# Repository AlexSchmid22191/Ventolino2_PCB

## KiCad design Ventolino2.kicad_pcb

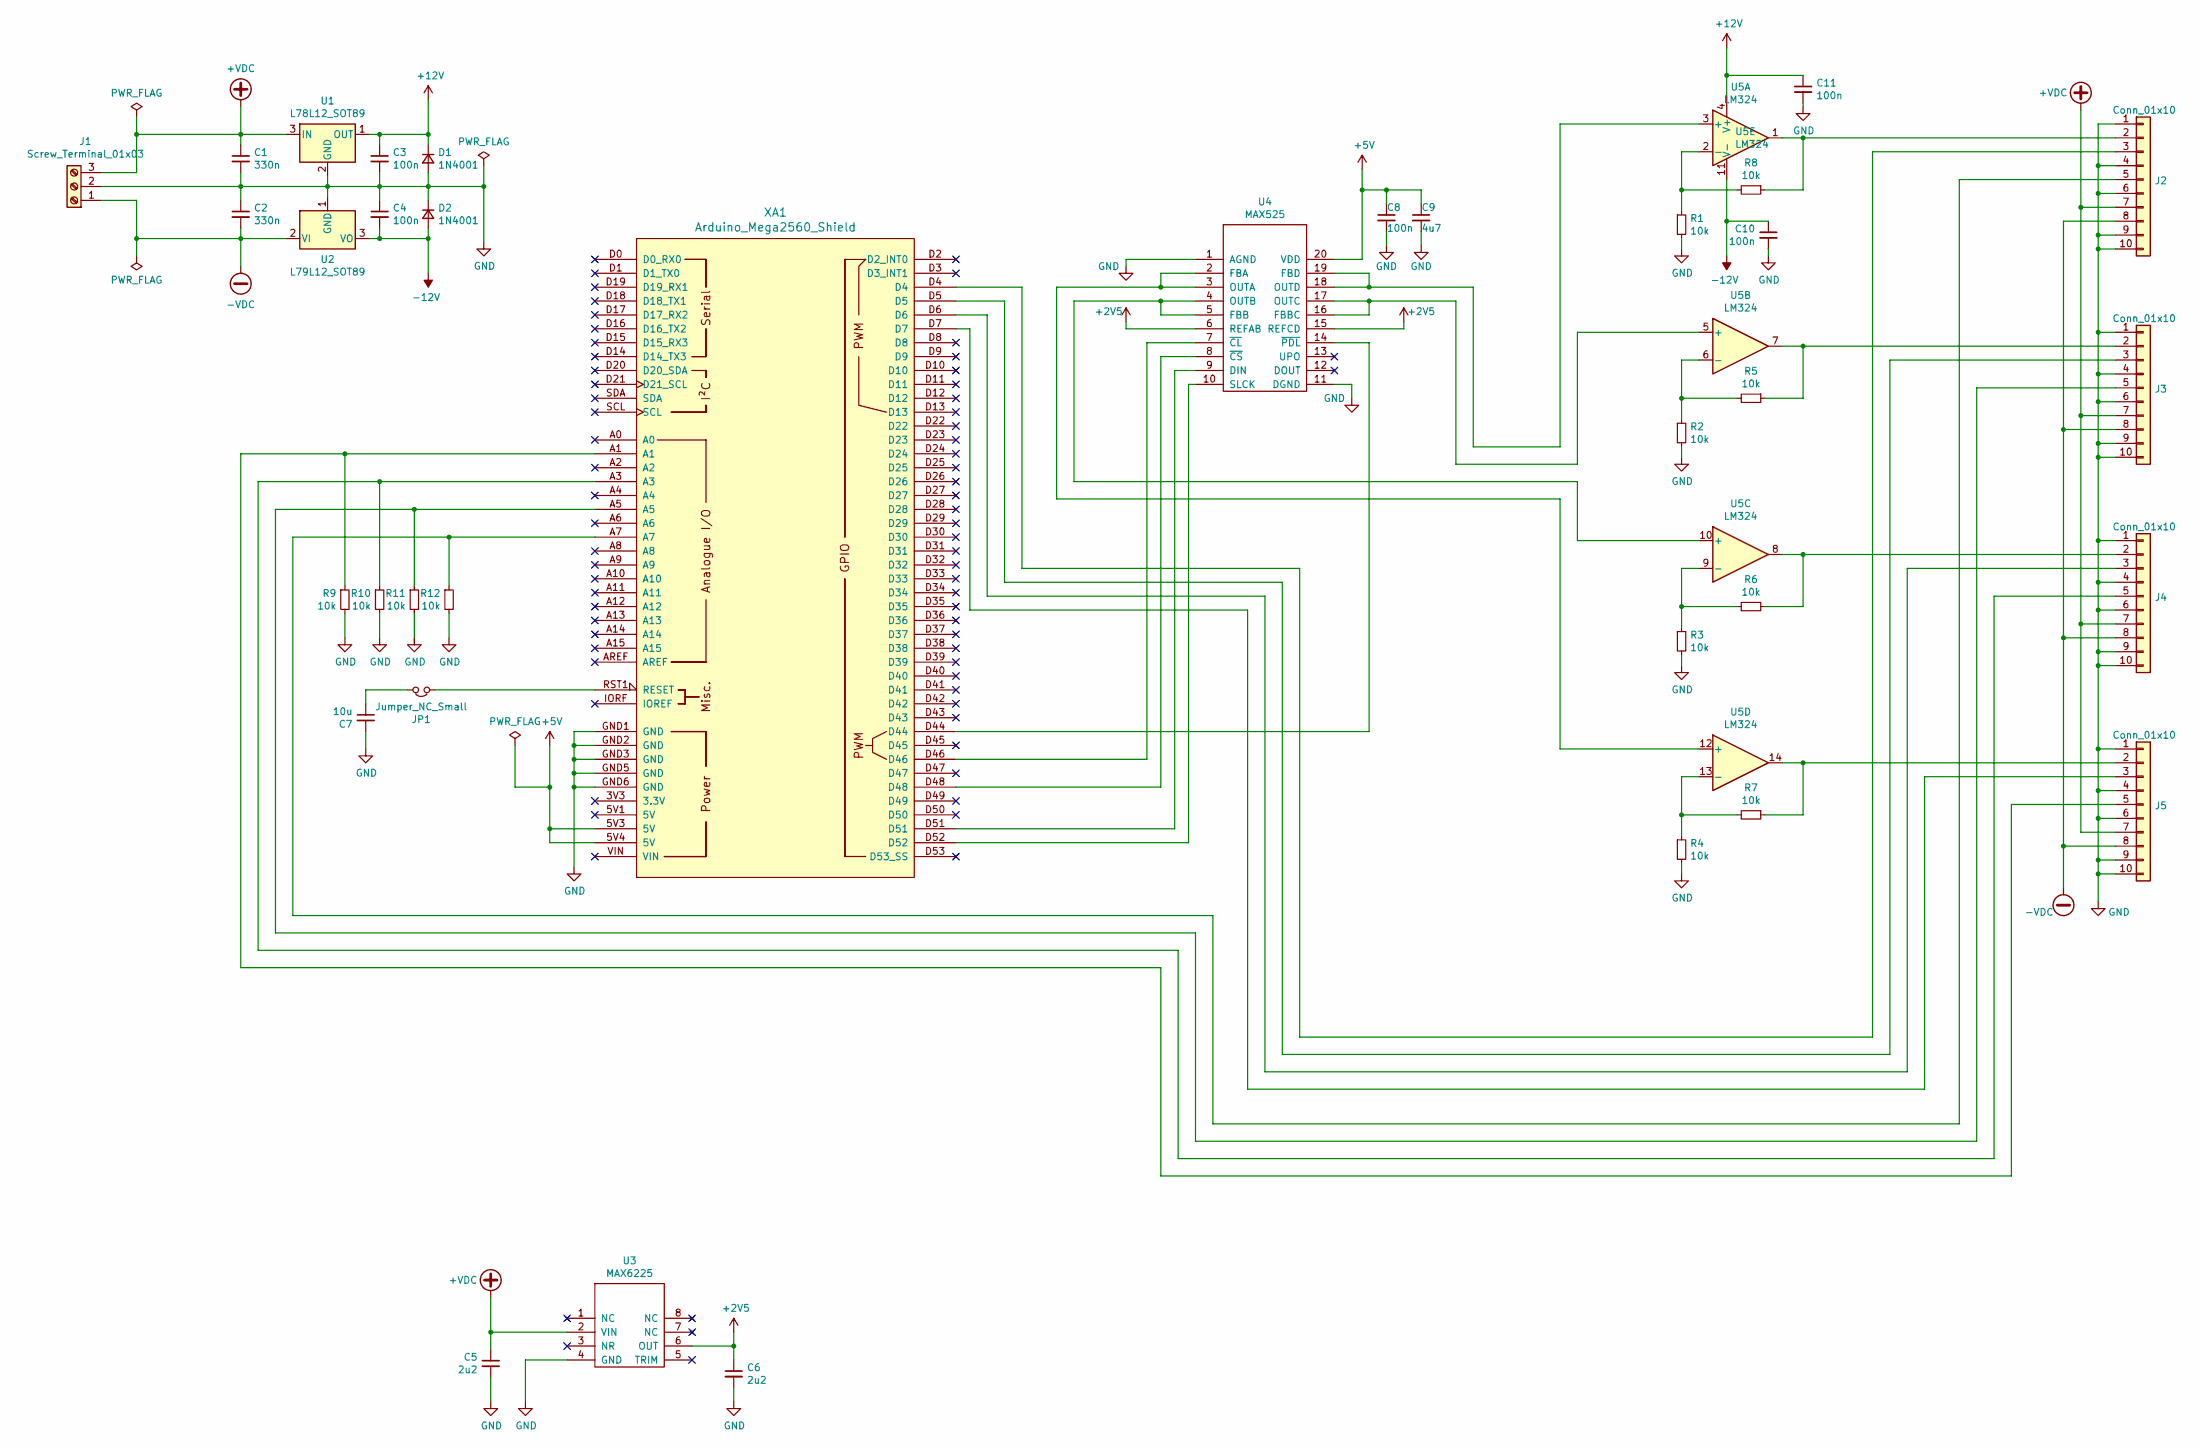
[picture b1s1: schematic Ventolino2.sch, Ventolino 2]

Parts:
C1, C2: 330n; C_0603_1608Metric_Pad1.05x0.95mm_HandSolder
C3, C4, C8, C10, C11: 100n; C_0603_1608Metric_Pad1.05x0.95mm_HandSolder
C5, C6: 2u2; C_0603_1608Metric_Pad1.05x0.95mm_HandSolder
C7: 10u; C_0603_1608Metric_Pad1.05x0.95mm_HandSolder
C9: 4u7; C_0603_1608Metric_Pad1.05x0.95mm_HandSolder
D1, D2: 1N4001; D_0603_1608Metric_Pad1.05x0.95mm_HandSolder
J1: Screw_Terminal_01x03; RS_Screw_Term_x3
J2, J3, J4, J5: Conn_01x10; IDC_05x02
JP1: Jumper_NC_Small; PinHeader_1x02_P2.54mm_Vertical
R1, R2, R3, R4, R5, R6, R7, R8, R9, R10, R11, R12: 10k; R_0603_1608Metric_Pad1.05x0.95mm_HandSolder
U1: L78L12_SOT89; SOT-89-3
U2: L79L12_SOT89; SOT-89-3
U3: MAX6225; DIP-8_W7.62mm_Socket
U4: MAX525; DIP-20_W7.62mm_Socket
U5: LM324; DIP-14_W7.62mm_Socket
XA1: Arduino_Mega2560_Shield; Arduino_Mega2560_Shield_mOD

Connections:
+2V5: C6.1, U3.6 (OUT), U4.6 (REFAB), U4.15 (REFCD)
+5V: C8.1, C9.1, U4.20 (VDD), XA1.5V3 (5V), XA1.5V4 (5V)
+12V: C3.1, C11.1, D1.1 (K), U1.1 (OUT), U5.4 (V+)
+VDC: C1.1, C5.1, J1.3, J2.7, J3.7, J4.7, J5.7, U1.3 (IN), U3.2 (VIN)
-12V: C4.2, C10.1, D2.2 (A), U2.3 (VO), U5.11 (V-)
-VDC: C2.2, J1.1, J2.8, J3.8, J4.8, J5.8, U2.2 (VI)
GND: C1.2, C2.1, C3.2, C4.1, C5.2, C6.2, C7.2, C8.2, C9.2, C10.2, C11.2, D1.2 (A), D2.1 (K), J1.2, J2.1, J2.4, J2.6, J2.9, J2.10, J3.1, J3.4, J3.6, J3.9, J3.10, J4.1, J4.4, J4.6, J4.9, J4.10, J5.1, J5.4, J5.6, J5.9, J5.10, R1.2, R2.2, R3.2, R4.2, R9.2, R10.2, R11.2, R12.2, U1.2 (GND), U2.1 (GND), U3.4 (GND), U4.1 (AGND), U4.11 (DGND), XA1.GND1 (GND), XA1.GND2 (GND), XA1.GND3 (GND), XA1.GND5 (GND), XA1.GND6 (GND)
unnamed: C7.1, JP1.2
unnamed: J2.2, R8.1, U5.1
unnamed: J2.3, XA1.D4
unnamed: J2.5, R12.1, XA1.A7
unnamed: J3.2, R5.1, U5.7
unnamed: J3.3, XA1.D5
unnamed: J3.5, R11.1, XA1.A5
unnamed: J4.2, R6.1, U5.8
unnamed: J4.3, XA1.D6
unnamed: J4.5, R10.1, XA1.A3
unnamed: J5.2, R7.1, U5.14
unnamed: J5.3, XA1.D7
unnamed: J5.5, R9.1, XA1.A1
unnamed: JP1.1, XA1.RST1 (RESET)
unnamed: R1.1, R8.2, U5.2 (-)
unnamed: R2.1, R5.2, U5.6 (-)
unnamed: R3.1, R6.2, U5.9 (-)
unnamed: R4.1, R7.2, U5.13 (-)
unnamed: U4.2 (FBA), U4.3 (OUTA), U5.12 (+)
unnamed: U4.4 (OUTB), U4.5 (FBB), U5.10 (+)
unnamed: U4.7 (~CL~), XA1.D46
unnamed: U4.8 (~CS~), XA1.D48
unnamed: U4.9 (DIN), XA1.D51
unnamed: U4.10 (SLCK), XA1.D52
unnamed: U4.14 (~PDL~), XA1.D44
unnamed: U4.16 (FBBC), U4.17 (OUTC), U5.5 (+)
unnamed: U4.18 (OUTD), U4.19 (FBD), U5.3 (+)

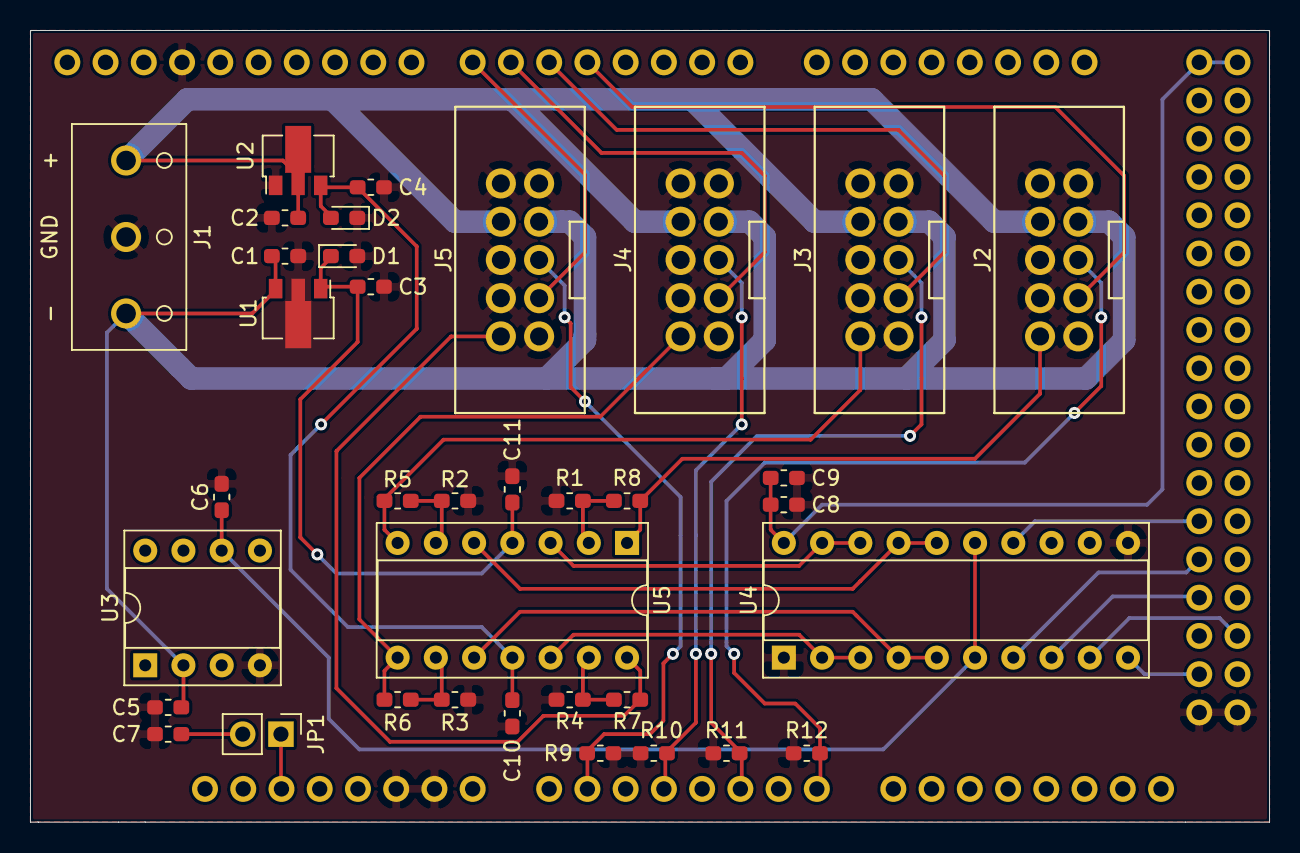
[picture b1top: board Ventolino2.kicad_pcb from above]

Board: 2 copper layers, 82.3 x 52.6 mm, 37 parts (0 on the bottom side), 34 nets.

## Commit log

2020-09-16 Redrew PCB in the old KiCad Format for compatibility
2020-09-30 Added a logo
